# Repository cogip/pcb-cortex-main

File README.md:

# Cortex motherboard Kicad project

## Install Kicad 4 on Ubuntu

```bash
sudo apt-add-repository ppa:js-reynaud/kicad-4
sudo apt-get update
sudo apt-get install kicad
```

## To open the project

Multiple projects are available:

```bash
kicad cortex_main.pro
kicad minus_main.pro
```

## Quick tutorial

- [WebCast on Youtube](https://www.youtube.com/watch?v=zK3rDhJqMu0)

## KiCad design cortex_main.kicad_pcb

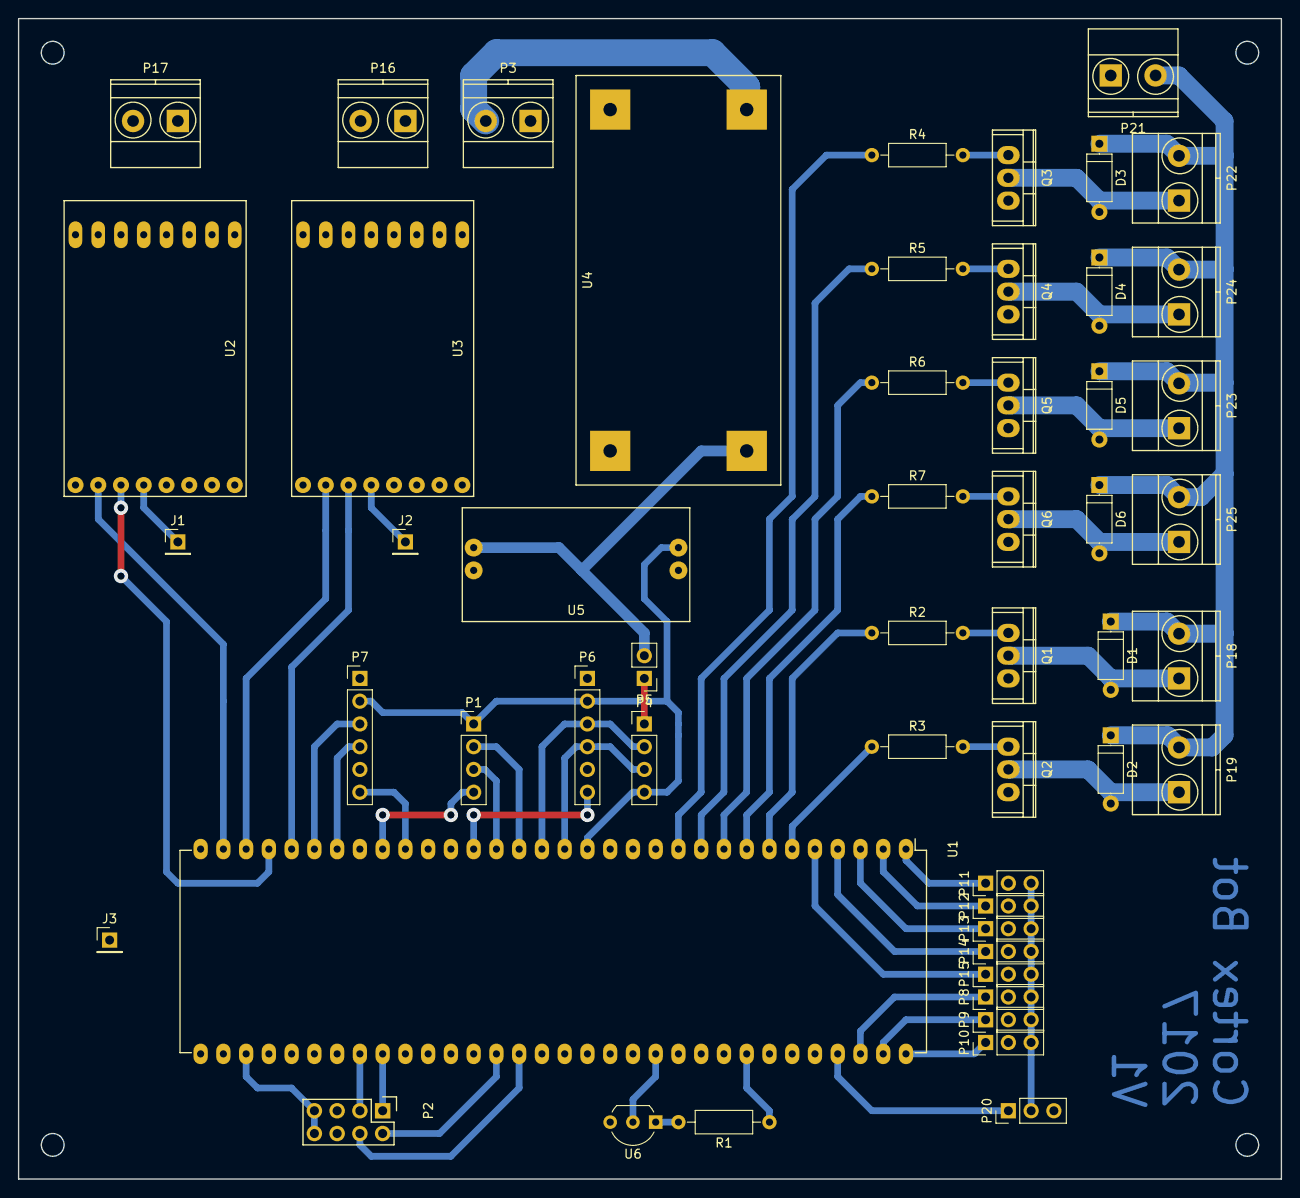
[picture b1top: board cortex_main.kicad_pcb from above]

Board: 2 copper layers, 141.0 x 129.5 mm, 53 parts (0 on the bottom side), 56 nets.

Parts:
D1, D2, D3, D4, D5, D6: 1N4001; D_A-405_P7.62mm_Horizontal
J1, J2, J3: TEST_1P; Pin_Header_Straight_1x01_Pitch2.54mm
P1, P4: CONN_01X04; Pin_Header_Straight_1x04_Pitch2.54mm
P2: CONN_02X04; Pin_Header_Straight_2x04
P3, P16, P17, P18, P19, P21, P22, P23, P24, P25: CONN_01X02; TerminalBlock_Pheonix_MKDS1.5-2pol
P5: CONN_01X02; Pin_Header_Straight_1x02_Pitch2.54mm
P6, P7: CONN_01X06; Pin_Header_Straight_1x06_Pitch2.54mm
P8, P9, P10, P11, P12, P13, P14, P15, P20: CONN_01X03; Pin_Header_Straight_1x03_Pitch2.54mm
Q1, Q2, Q3, Q4, Q5, Q6: IRF540N; TO-220
R1: 1K; R_Axial_DIN0207_L6.3mm_D2.5mm_P10.16mm_Horizontal
R2, R3, R4, R5, R6, R7: 100R; R_Axial_DIN0207_L6.3mm_D2.5mm_P10.16mm_Horizontal
U1: socket_leon_x3_dil64; DIP-64_W22.86mm_LongPads
U2, U3: socket_pololu_24v12; pololu_24v12_dip
U4: socket_lm2596_mod; lm2596s_mod
U5: socket_ams1117-3V3_mod; ams1117-3V3_mod
U6: MCP100-D; TO-92_Inline_Wide

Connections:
+3V3: P1.1, P2.7, P2.8, P4.4, P6.2, P7.2, P20.1, U1.15, U1.25, U1.35, U1.45, U1.53, U1.61, U5.3, U6.2
+5V: P5.2, P20.3, U4.3, U5.1
+24V: P3.2, U2.1, U2.2, U2.15, U2.16, U3.1, U3.2, U3.15, U3.16, U4.1
/Sheet_Connectors/RGB_LEDEN_L: P6.6, U1.20
/Sheet_Connectors/RGB_LEDEN_R: P7.6, U1.23
/Sheet_Connectors/SCL_C: P4.2, P6.3, U1.17
/Sheet_Connectors/SCL_D: P7.3, U1.27
/Sheet_Connectors/SDA_C: P4.3, P6.4, U1.16
/Sheet_Connectors/SDA_D: P7.4, U1.26
/Sheet_Connectors/UART_DBG_RXD: P1.3, U1.19
/Sheet_Connectors/UART_DBG_TXD: P1.2, U1.18
/Sheet_MCU/CMD_ARMMOTOR_L: R2.1, U1.7
/Sheet_MCU/CMD_ARMMOTOR_R: R3.1, U1.6
/Sheet_MCU/CMD_PUMP_BL: R6.1, U1.9
/Sheet_MCU/CMD_PUMP_BR: R7.1, U1.8
/Sheet_MCU/CMD_PUMP_TL: R4.1, U1.11
/Sheet_MCU/CMD_PUMP_TR: R5.1, U1.10
/Sheet_MCU/DIR_L: U1.31, U2.10
/Sheet_MCU/DIR_R: U1.30, U3.10
/Sheet_MCU/PWM_L: U1.29, U2.11
/Sheet_MCU/PWM_R: U1.28, U3.11
ENCA_L: P2.3, U1.40
ENCA_R: P2.4, U1.47
ENCB_L: P2.1, U1.41
ENCB_R: P2.2, U1.46
GND: J3.1, P1.4, P2.5, P2.6, P3.1, P4.1, P5.1, P6.1, P7.1, P8.2, P9.2, P10.2, P11.2, P12.2, P13.2, P14.2, P15.2, P21.1, Q1.3, Q2.3, Q3.3, Q4.3, Q5.3, Q6.3, U1.14, U1.24, U1.34, U1.44, U1.52, U1.60, U2.7, U2.8, U2.9, U3.7, U3.8, U3.9, U4.2, U4.4, U5.2, U5.4, U6.3
IR_VCC: P8.3, P9.3, P10.3, P11.3, P12.3, P13.3, P14.3, P15.3, P20.2
IR_VIN_0: P8.1, U1.62
IR_VIN_1: P9.1, U1.63
IR_VIN_2: P10.1, U1.64
IR_VIN_3: P11.1, U1.1
IR_VIN_4: P12.1, U1.2
IR_VIN_5: P13.1, U1.3
IR_VIN_6: P14.1, U1.4
IR_VIN_7: P15.1, U1.5
unnamed: J1.1, U2.12
unnamed: J2.1, U3.12
unnamed: Q1.1, R2.2
unnamed: Q2.1, R3.2
unnamed: Q3.1, R4.2
unnamed: Q4.1, R5.2
unnamed: Q5.1, R6.2
unnamed: Q6.1, R7.2
unnamed: R1.1, U1.57
unnamed: R1.2, U6.1
OUTA_L: P17.1, U2.3, U2.4
OUTA_R: P16.1, U3.3, U3.4
OUTB_L: P17.2, U2.5, U2.6
OUTB_R: P16.2, U3.5, U3.6
OUTN_ARMMOTOR_L: D1.2, P18.1, Q1.2
OUTN_ARMMOTOR_R: D2.2, P19.1, Q2.2
OUTN_PUMP_BL: D5.2, P23.1, Q5.2
OUTN_PUMP_BR: D6.2, P25.1, Q6.2
OUTN_PUMP_TL: D3.2, P22.1, Q3.2
OUTN_PUMP_TR: D4.2, P24.1, Q4.2
OUTP_ARMMOTOR_L: D1.1, D2.1, D3.1, D4.1, D5.1, D6.1, P18.2, P19.2, P21.2, P22.2, P23.2, P24.2, P25.2

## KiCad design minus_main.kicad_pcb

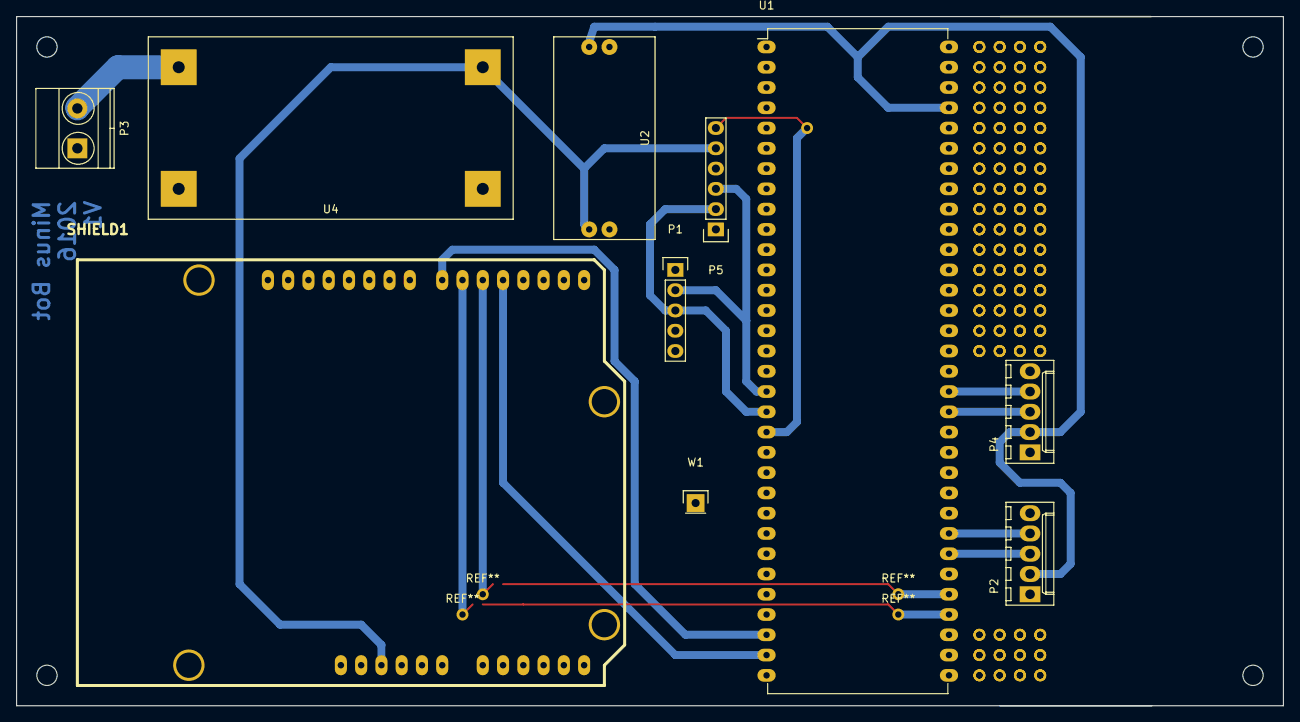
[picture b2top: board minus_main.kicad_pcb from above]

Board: 2 copper layers, 158.8 x 86.4 mm, 10 parts (0 on the bottom side), 15 nets.

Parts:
P1: CONN_01X05; Pin_Header_Straight_1x05
P2, P4: CONN_01X05; Molex_KK-6410-05_05x2.54mm_Straight
P3: CONN_01X02; TerminalBlock_Pheonix_MKDS1.5-2pol
P5: CONN_01X06; Pin_Header_Straight_1x06
SHIELD1: arduino_shield
U1: socket_leon_x3_dil64; DIP-64_W22.86mm_LongPads
U2: socket_ams1117-3V3_mod; ams1117-3V3_mod
U4: socket_lm2596_mod; lm2596s_mod
W1: TEST_1P; Pin_Header_Straight_1x01

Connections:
+3V3: P2.2, P4.2, U1.61, U2.3
+5V: P5.5, SHIELD1.5V, U2.1, U4.3
+24V: P3.2, U4.1
/Sheet_Connectors/BT_KEY: P5.6, U1.20
/Sheet_Connectors/BT_RXD: P1.3, P5.2, U1.19
/Sheet_Connectors/BT_TXD: P1.2, P5.3, U1.18
/Sheet_MCU/DIR_L: SHIELD1.7, U1.30
/Sheet_MCU/DIR_R: SHIELD1.4, U1.31
/Sheet_MCU/PWM_L: SHIELD1.6, U1.36
/Sheet_MCU/PWM_R: SHIELD1.5, U1.37
ENCA_L: P2.3, U1.39
ENCA_R: P4.3, U1.46
ENCB_L: P2.4, U1.40
ENCB_R: P4.4, U1.47
GND: P1.4, P2.1, P3.1, P4.1, P5.4, SHIELD1.GND1, SHIELD1.GND2, U1.14, U1.24, U1.34, U1.44, U1.52, U1.60, U2.2, U2.4, U4.2, U4.4, W1.1

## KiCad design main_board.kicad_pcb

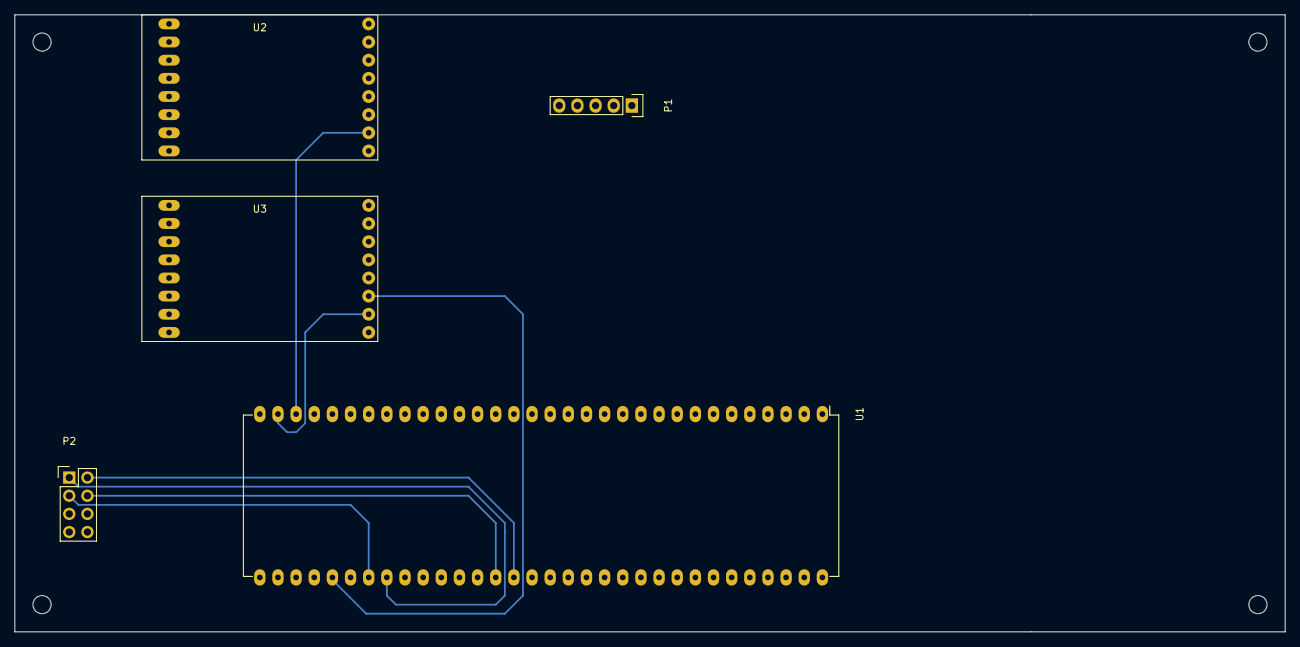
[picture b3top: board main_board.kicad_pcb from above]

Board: 2 copper layers, 177.8 x 86.4 mm, 5 parts (0 on the bottom side), 17 nets.

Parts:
P1: CONN_01X05; Pin_Header_Straight_1x05
P2: CONN_02X04; Pin_Header_Straight_2x04
U1: socket_leon_x3_dil64; DIP-64_W22.86mm_LongPads
U2, U3: socket_pololu_24v12; pololu_24v12_dip

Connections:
+3V3: P2.5, P2.6
+24V: U2.1, U2.2, U2.15, U2.16, U3.1, U3.2, U3.15, U3.16
/Sheet_Connectors/UART_DBG_RXD: P1.3, U1.19
/Sheet_Connectors/UART_DBG_TXD: P1.2, U1.18
/Sheet_MCU/DIR_L: U1.30, U2.10
/Sheet_MCU/DIR_R: U1.31, U3.10
/Sheet_MCU/PWM_L: U1.36, U2.11
/Sheet_MCU/PWM_R: U1.37, U3.11
/Sheet_Motors/OUTA_L: U2.3, U2.4
/Sheet_Motors/OUTA_R: U3.3, U3.4
/Sheet_Motors/OUTB_L: U2.5, U2.6
/Sheet_Motors/OUTB_R: U3.5, U3.6
ENCA_L: P2.3, U1.39
ENCA_R: P2.4, U1.46
ENCB_L: P2.1, U1.40
ENCB_R: P2.2, U1.47
GND: P1.4, P2.7, P2.8, U2.7, U2.8, U2.9, U3.7, U3.8, U3.9

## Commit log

2016-07-26 initial commit
    a library for Leon Instrument X3-DIL64 module as been created.
2016-07-26 README.md: creation
2016-07-30 lib: rename to be more generic
2016-07-30 all: add pololu 24v12 footprint and symbol
2016-07-30 pcb: add dimensions
    same as geonobot "xmega_board" pcb.
2016-07-30 pcb: fix width size
2016-07-31 pcb: routing test and holes
2016-08-01 all: add UARTC0 (debug link)
2016-08-03 sch: move to hierarchical schematic and multiple sheets
2016-10-15 bot_parts: add lm2596s module symbol & footprint
2016-10-15 sch: add main_board_psu
    subsheet contains PSU relevant parts
2016-10-15 all: add .gitignore
    hide backup file for initial file release
2016-10-15 libs: place in a subdir
2016-10-15 all: rename project for multiple bots support
2016-10-15 all: introduce minus main project
2016-10-15 libs: move bot_part footprint in subdir
    this is required by footprint editor to correctly view parts
    of a lib, otherwise all footprint from multiple lib will be
    visible from one lib...
2016-10-15 minus: h-bridge: switch to DFRobot L298P shield
    previously, pololu were on schematic.
2016-10-15 libs: add arduino shield library
    easy integration of opensource lib from:
    http://www.thingiverse.com/thing:9630
    this will ease the dfrobot hbridge shield.
2016-10-16 minus: add encoder connectors
    pcb update
2016-10-16 lib: new ams1117-3V3 symbol & footprint
2016-10-16 minus: add 3V3 module on schematic & pcb
2016-10-16 minus: add a lots of pads for development
2016-10-16 README.md: update
2016-10-20 minus: add BT HC-05 module on schematic & pcb
2016-10-20 minus: add a GND testpad
    This is intented to get an easy access to GND reference
    for electrical measurement on board.
2017-02-22 cortex: update to 120x120mm PCB size
    To match final mechanical constraints
2017-02-22 cortex: add 3V3 regulator
2017-02-22 cortex: fix left engine encoder gpio
    wiring was shift on minus, now it to match current fw gpio muxing
2017-02-22 cortex: add I2C bus & connectors to SD21 extension board
2017-02-22 lib: new MCP100-D symbol & footprint
    Reset signal generator from Microchip
    http://ww1.microchip.com/downloads/en/DeviceDoc/11187f.pdf
2017-02-22 cortex: add MCP100-D to reset MCU
2017-02-26 cortex: rename main I2C bus to specify PortC
    This is in prevision of introducing another I2C bus
    on another Port.
2017-02-26 cortex: add I2CD and RGB sensors
    schematic only
2017-02-26 cortex: add SD21 I2C address on schematic
2017-02-26 cortex: pcb: place RGB connectors
2017-02-26 cortex: fixup MCU sheet signals direction
    for cosmetics only. unfortunately, this is not propagated on
    root sheet... hum.
2017-02-26 cortex: add Sharp IR sensors connectors
    on schematic & pcb.
2017-02-26 cortex: add Motors connectors
    on sch & pcb.
2017-02-26 cortex: pcb: start output layout
2017-02-26 cortex: pcb move on
    some new stuff. sd21, and few routing tests
2017-02-26 cortex: new pin muxing to ease pcb layout
    pcb layout progress as well
2017-02-26 cortex: add Arms Motor mosfet drivers
2017-02-26 cortex: add clamping diode to arm motor mosfet
2017-02-26 cortex: update UART connector
    move to 4pins and wire the +3V3 supply for comm module.
2017-03-13 cortex: sch & pcb updates after first review
    - add testpad on pololu /rst signals
    - fix rotary encoders pinout: [+,-,A,B]
    - add jumper to choose 3V3 or 5V for IR sharp sensors
2017-03-14 cortex: add vacuum pump mosfets
    on both schematic & layout.
2017-03-16 cortex: update arm motors PSU
    PCB is almost done.
2017-03-16 cortex: add gnd test pad and text on PCB
2017-03-22 cortex: enhance pcb routing
    power track are now bigger
